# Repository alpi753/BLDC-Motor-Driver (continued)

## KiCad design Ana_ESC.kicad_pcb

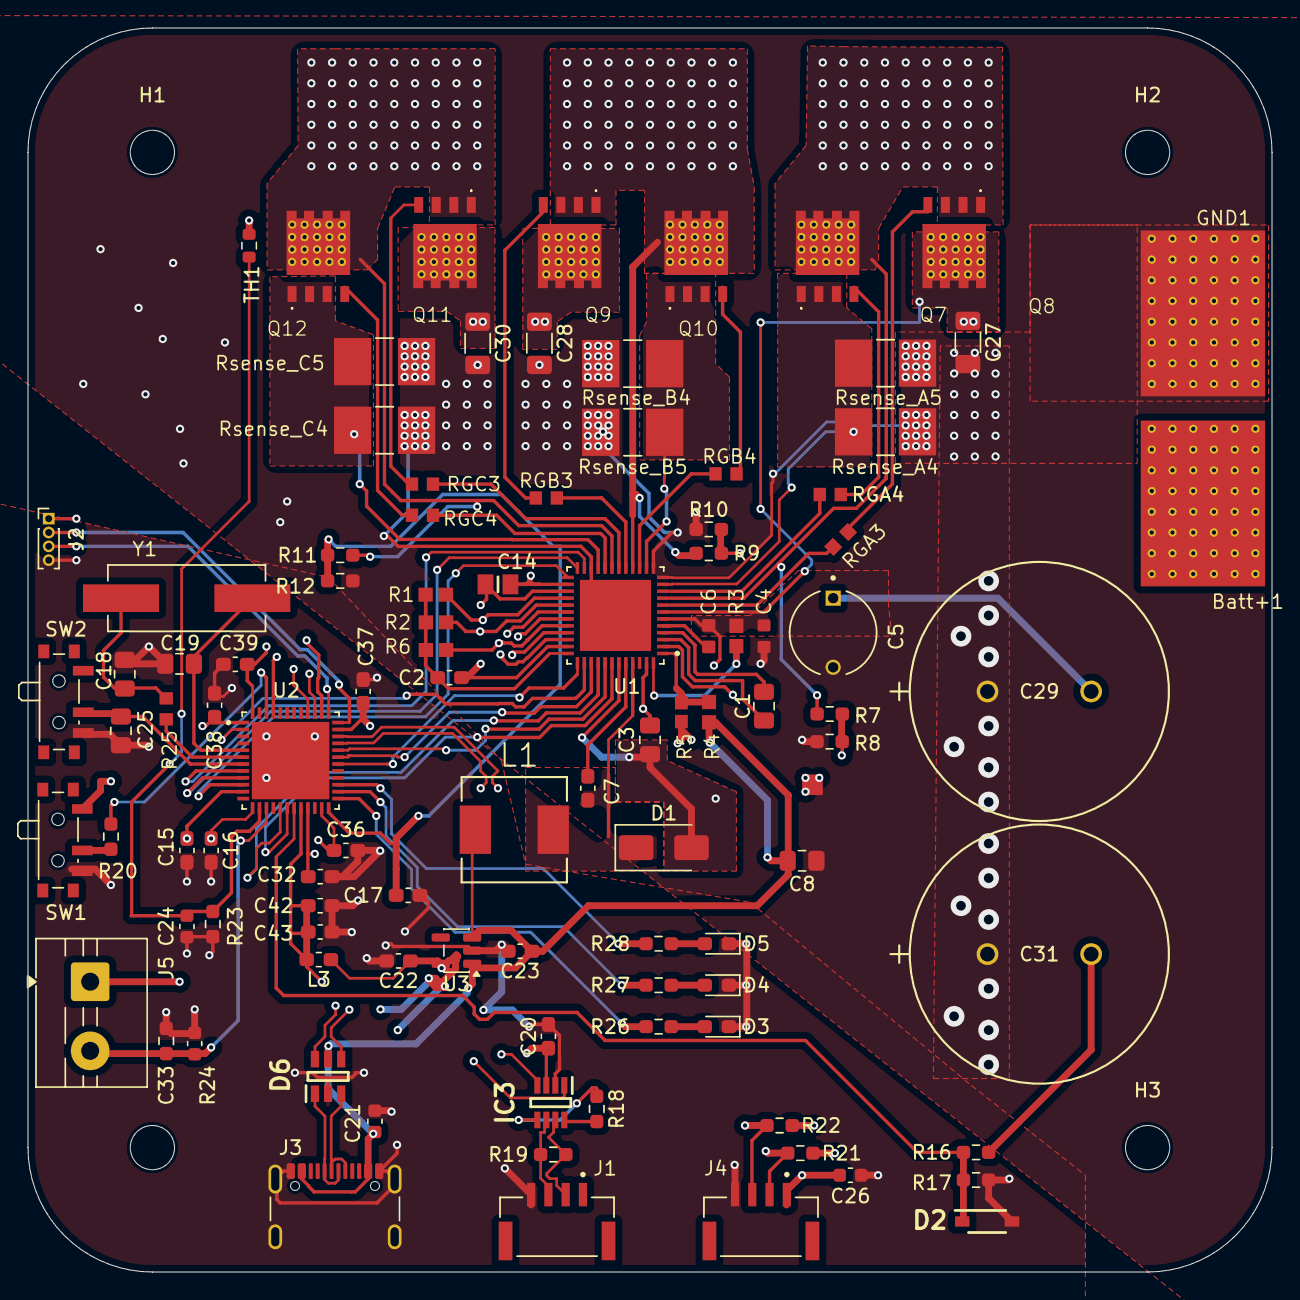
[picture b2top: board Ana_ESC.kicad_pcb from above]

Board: 4 copper layers, 90.0 x 90.0 mm, 105 parts (0 on the bottom side), 79 nets.

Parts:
Batt+1: power_pad_smd; Power_pad_smd
C1, C3: 47nF 100V; C_0805_2012Metric_Pad1.18x1.45mm_HandSolder
C2: 1uF 6.3V; C_0603_1608Metric_Pad1.08x0.95mm_HandSolder
C4: 0.1 uF 100V; CAPC1608X90N
C5: 22uF 100V; CAPPRD500W50D630H1120
C6: 1uF 16V; CAPC1608X90N
C7: 0.1uF 16V; C_0603_1608Metric_Pad1.08x0.95mm_HandSolder
C8: 22uF 16V; C_0805_2012Metric_Pad1.18x1.45mm_HandSolder
C14: 0.1uF 6.3V; CAPC2012X140N
C15, C16, C17, C43: 10nF; C_0603_1608Metric_Pad1.08x0.95mm_HandSolder
C18, C19: 33pF; C_0805_2012Metric_Pad1.18x1.45mm_HandSolder
C20, C37, C38, C39: 100nF; C_0603_1608Metric_Pad1.08x0.95mm_HandSolder
C21, C26: 1uF; C_0603_1608Metric
C22, C23: 1u; C_0603_1608Metric_Pad1.08x0.95mm_HandSolder
C24, C33: 2.2uF; C_0603_1608Metric
C25: 100nF; C_0805_2012Metric_Pad1.18x1.45mm_HandSolder
C27, C28, C30: 2.2uF; C_1206_3216Metric_Pad1.33x1.80mm_HandSolder
C29, C31: 680uF 80V; 80ZLJ680MGC18X25
C32: 100n; C_0603_1608Metric_Pad1.08x0.95mm_HandSolder
C36: 4u7; C_0603_1608Metric_Pad1.08x0.95mm_HandSolder
C42: 1uF; C_0603_1608Metric_Pad1.08x0.95mm_HandSolder
D1: 80V 1A; D_SMA
D2: D_Zener; SOD3716X135N
D3: LEDA; LED_0603_1608Metric_Pad1.05x0.95mm_HandSolder
D4: LEDB; LED_0603_1608Metric_Pad1.05x0.95mm_HandSolder
D5: LEDC; LED_0603_1608Metric_Pad1.05x0.95mm_HandSolder
D6: USBLC6-2SC6Y; SOT95P280X145-6N
GND1: power_pad_smd; Power_pad_smd
H1, H2, H3, H4: MountingHole; MountingHole_3.2mm_M3
IC3: TCAN330DCNT; SOT65P280X145-8N
J1, J4: BM04B-GHS-TBT_LF__SN__N_; JST_BM04B-GHS-TBT_LF__SN__N_
J2: Conn_01x04_Pin; PinHeader_1x04_P1.00mm_Vertical
J3: USB_C_Receptacle_USB2.0_16P; USB_C_Receptacle_GCT_USB4105-xx-A_16P_TopMnt_Horizontal
J5: Conn_01x02_Socket; TerminalBlock_MaiXu_MX126-5.0-02P_1x02_P5.00mm
L1: 22uH 1.6A; INDM7676X355N
L3: 100MHz / 1kR; L_0603_1608Metric_Pad1.05x0.95mm_HandSolder
NT2: NetTie_4; NetTie-4_SMD_Pad0.5mm
Q7, Q8, Q9, Q10, Q11, Q12: STL90N6F7; STL90N6F7_Thermal_Vias
R1, R2, R6: 10K; RESC1607X60N
R3: 100K; RESC1607X60N
R4: 5k6; RESC1607X60N
R5: 1k; RESC1508X50N
R7, R9, R11: 91k; R_0603_1608Metric_Pad0.98x0.95mm_HandSolder
R8, R10, R12: 4k7; R_0603_1608Metric_Pad0.98x0.95mm_HandSolder
R16: 3.3k; R_0603_1608Metric_Pad0.98x0.95mm_HandSolder
R17: 100k; R_0603_1608Metric_Pad0.98x0.95mm_HandSolder
R18, R20, R21, R22: 10k; R_0603_1608Metric_Pad0.98x0.95mm_HandSolder
R19: 120R; R_0603_1608Metric_Pad0.98x0.95mm_HandSolder
R23, R24: R_Small; R_0603_1608Metric_Pad0.98x0.95mm_HandSolder
R25: 0 ohm; RESC1508X55N
R26, R27, R28: 330R; R_0603_1608Metric_Pad0.98x0.95mm_HandSolder
RGA3, RGA4: 0ohm; RESC1508X55N
RGB3, RGB4: 0ohm; RESC1508X55N
RGC3, RGC4: 0ohm; RESC1508X55N
Rsense_A4, Rsense_A5: 2mohm; RESC6432X80N
Rsense_B4, Rsense_B5: 2mohm; RESC6432X80N
Rsense_C4, Rsense_C5: 2mohm; RESC6432X80N
SW1, SW2: SW_SPDT; SW_SPDT_PCM12
TH1: ERT-J1VG103FA; R_0603_1608Metric
U1: DRV8323RSRGZR; QFN50P700X700X100-49N
U2: STM32G431CBU6; QFN50P700X700X60-49N
U3: ME6211C33M5; SOT-23-5
Y1: ECS-80-20-5PX-TR; XTAL_ECS-80-20-5PX-TR

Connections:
+3.3V: C14.2, C20.1, C22.1, C26.1, C36.1, C37.1, C38.1, C39.1, IC3.3 (VCC), J2.1, J4.1, J5.1, L3.1, R21.1, R22.1, SW1.1 (A), TH1.1, U1.26 (VREF), U2.1 (VBAT), U2.23 (VDD), U2.35 (VDD), U2.48 (VDD), U3.5 (V_{OUT})
+3.3VA: C32.1, C42.1, C43.1, L3.2, U2.20 (VREF+), U2.21 (VDDA)
/Gate_Driver/AGND: C2.2, C14.1, NT2.4, R5.2, U1.27 (DGND), U1.35 (AGND)
/Gate_Driver/BGND: C3.1, D1.2 (A), NT2.2, U1.43 (BGND)
/Gate_Driver/DVDD: C2.1, R1.2, R2.2, R6.2, U1.36 (DVDD)
/Gate_Driver/FAULT: R1.1, U1.28 (FAULT_N)
/Gate_Driver/GHA: RGA3.1, U1.8 (GHA)
/Gate_Driver/GHB: RGB3.1, U1.17 (GHB)
/Gate_Driver/GHC: RGC3.1, U1.18 (GHC)
/Gate_Driver/GLA: RGA4.1, U1.10 (GLA)
/Gate_Driver/GLB: RGB4.1, U1.15 (GLB)
/Gate_Driver/GLC: RGC4.1, U1.20 (GLC)
/Gate_Driver/INHA: U1.37 (INHA), U2.30 (PA8)
/Gate_Driver/INHB: U1.39 (INHB), U2.31 (PA9)
/Gate_Driver/INHC: U1.41 (INHC), U2.32 (PA10)
/Gate_Driver/INLA: U1.38 (INLA), U2.2 (PC13)
/Gate_Driver/INLB: U1.40 (INLB), U2.17 (PB0)
/Gate_Driver/INLC: U1.42 (INLC), U2.18 (PB1)
/Gate_Driver/PGND: NT2.3, U1.2 (PGND)
/Gate_Driver/SCS: R6.1, U1.32 (SCS_N)
/Gate_Driver/SDO: R2.1, U1.29 (SDO)
/Gate_Driver/SENS1: C15.1, R7.2, R8.2, U2.11 (PA3)
/Gate_Driver/SENS2: C16.1, R9.2, R10.2, U2.13 (PA5)
/Gate_Driver/SENS3: C17.1, R11.2, R12.2, U2.24 (PB11)
/Gate_Driver/SHA: Q7.1 (S_1), Q7.2 (S_2), Q7.3 (S_3), Q8.5 (D_1), Q8.6 (D_2), Q8.7 (D_3), Q8.8 (D_4), Q8.9 (D_5), R7.1, U1.9 (SHA)
/Gate_Driver/SHB: Q9.1 (S_1), Q9.2 (S_2), Q9.3 (S_3), Q10.5 (D_1), Q10.6 (D_2), Q10.7 (D_3), Q10.8 (D_4), Q10.9 (D_5), R9.1, U1.16 (SHB)
/Gate_Driver/SHC: Q11.1 (S_1), Q11.2 (S_2), Q11.3 (S_3), Q12.5 (D_1), Q12.6 (D_2), Q12.7 (D_3), Q12.8 (D_4), Q12.9 (D_5), R11.1, U1.19 (SHC)
/Gate_Driver/SOA: U1.25 (SOA), U2.10 (PA2)
/Gate_Driver/SOB: U1.24 (SOB), U2.9 (PA1)
/Gate_Driver/SOC: U1.23 (SOC), U2.8 (PA0)
/Gate_Driver/SPB: Q10.1 (S_1), Q10.2 (S_2), Q10.3 (S_3), Rsense_B4.2, Rsense_B5.2, U1.14 (SPB)
/Gate_Driver/SPC: Q12.1 (S_1), Q12.2 (S_2), Q12.3 (S_3), Rsense_C4.2, Rsense_C5.2, U1.21 (SPC)
/MCU/BOOT0: R20.2, U2.46 (PB8-BOOT0)
/MCU/CAN+: IC3.7 (CANH), J1.2, R19.2
/MCU/CAN-: IC3.6 (CANL), J1.3, R19.1
/MCU/D+: D6.3 (I/O2_1), J3.A6 (D+), J3.B6 (D+)
/MCU/D-: D6.1 (I/O1_1), J3.A7 (D-), J3.B7 (D-)
/MCU/I2C1_SCL: J4.2, R21.2, U2.38 (PA15)
/MCU/I2C1_SDA: J4.3, R22.2, U2.45 (PB7)
/MCU/NTC_FET: C24.1, R23.1, TH1.2, U2.14 (PA6)
/MCU/NTC_MTR: C33.1, J5.2, R24.1, U2.15 (PA7)
/MCU/PD2: IC3.8 (S), R18.2
/MCU/RST: C25.1, SW2.2 (B), U2.7 (PG10-~RST)
/MCU/SWCLK: J2.3, U2.37 (PA14)
/MCU/SWDIO: J2.2, U2.36 (PA13)
/MCU/UART_N: IC3.4 (RXD), U2.39 (PC10)
/MCU/UART_P: IC3.1 (TXD), U2.40 (PC11)
/MCU/USB_DN: D6.6 (I/O1_2), U2.33 (PA11)
/MCU/USB_DP: D6.4 (I/O2_2), U2.34 (PA12)
/MCU/VBus: D2.1 (K), R16.2, R17.1, U2.19 (PB2)
/Mosfetv2/A+: Q8.1 (S_1), Q8.2 (S_2), Q8.3 (S_3), Rsense_A4.2, Rsense_A5.2, U1.11 (SPA)
GND: C15.2, C16.2, C17.2, C18.2, C19.2, C20.2, C21.2, C22.2, C23.2, C24.2, C25.2, C26.2, C32.2, C33.2, C36.2, C37.2, C38.2, C39.2, C42.2, C43.2, D2.2 (A), D3.1 (K), D4.1 (K), D5.1 (K), D6.2 (GND), IC3.2 (GND), J1.4, J2.4, J3.A1 (GND), J3.A12 (GND), J3.B1 (GND), J3.B12 (GND), J3.S1 (SHIELD), J4.4, R17.2, R23.2, R24.2, SW1.3 (C), SW2.3 (C), U2.49 (VSS), U3.2 (V_{SS})
MCU_PWR: C8.2, C21.1, C23.1, D6.5 (VBUS), J3.A4 (VBUS), J3.A9 (VBUS), J3.B4 (VBUS), J3.B9 (VBUS), L1.1, R4.2, U3.1 (V_{IN}), U3.3 (CE)
unnamed: C18.1, R25.1, Y1.1
unnamed: C7.1, D1.1 (K), L1.2, U1.45 (SW)
unnamed: D3.2 (A), R26.1
unnamed: D4.2 (A), R27.1
unnamed: D5.2 (A), R28.1
unnamed: IC3.5 (SHDN), R18.1
unnamed: Q7.4 (G), RGA3.2
unnamed: Q8.4 (G), RGA4.2
unnamed: Q9.4 (G), RGB3.2
unnamed: Q10.4 (G), RGB4.2
unnamed: Q11.4 (G), RGC3.2
unnamed: Q12.4 (G), RGC4.2
unnamed: R20.1, SW1.2 (B)
unnamed: C7.2, U1.44 (CB)
unnamed: C1.2, U1.4 (CPH)
unnamed: C1.1, U1.3 (CPL)
unnamed: R4.1, R5.1, U1.1 (FB)
unnamed: R3.2, U1.48 (SHDN_N)
unnamed: C6.1, U1.5 (VCP)
unnamed: R26.2, U2.25 (PB12)
unnamed: R27.2, U2.26 (PB13)
unnamed: R28.2, U2.27 (PB14)
unnamed: C19.1, U2.5 (PF0-OSC_IN), Y1.2
unnamed: R25.2, U2.6 (PF1-OSC_OUT)
PGND_DRV: C4.2, C5.N, C8.1, C27.2, C28.2, C29.1, C30.2, C31.1, GND1.1, NT2.1, R8.1, R10.1, R12.1, Rsense_A4.1, Rsense_A5.1, Rsense_B4.1, Rsense_B5.1, Rsense_C4.1, Rsense_C5.1, U1.12 (SNA), U1.13 (SNB), U1.22 (SNC), U1.49 (EP)
VM: Batt+1.1, C3.2, C4.1, C5.P, C6.2, C27.1, C28.1, C29.2, C30.1, C31.2, Q7.5 (D_1), Q7.6 (D_2), Q7.7 (D_3), Q7.8 (D_4), Q7.9 (D_5), Q9.5 (D_1), Q9.6 (D_2), Q9.7 (D_3), Q9.8 (D_4), Q9.9 (D_5), Q11.5 (D_1), Q11.6 (D_2), Q11.7 (D_3), Q11.8 (D_4), Q11.9 (D_5), R3.1, R16.1, U1.6 (VM), U1.7 (VDRAIN), U1.47 (VIN)

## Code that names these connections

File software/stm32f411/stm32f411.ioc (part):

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Mcu.Name=STM32F411C(C-E)Ux
Mcu.Package=UFQFPN48
Mcu.UserName=STM32F411CEUx
PA0-WKUP.GPIOParameters=GPIO_Label
PA0-WKUP.GPIO_Label=ADC_Ph0_Curr
PA0-WKUP.Signal=ADCx_IN0
PA1.GPIOParameters=GPIO_Label
PA1.GPIO_Label=ADC_Ph1_Curr
PA1.Signal=ADCx_IN1
PA10.GPIOParameters=GPIO_Label
PA10.GPIO_Label=INHC
PA10.Signal=S_TIM1_CH3
PA11.Mode=Device_Only
PA11.Signal=USB_OTG_FS_DM
PA12.Mode=Device_Only
PA12.Signal=USB_OTG_FS_DP
PA13.Mode=Serial_Wire
PA13.Signal=SYS_JTMS-SWDIO
PA14.Mode=Serial_Wire
PA14.Signal=SYS_JTCK-SWCLK
PA2.GPIOParameters=GPIO_Label
PA2.GPIO_Label=ADC_Ph2_Curr
PA2.Signal=ADCx_IN2
PA3.GPIOParameters=GPIO_Label
PA3.GPIO_Label=SENS1
PA3.Signal=GPIO_Input
PA4.Signal=GPIO_Input
PA5.GPIOParameters=GPIO_Label
PA5.GPIO_Label=V_Bus_Sense
PA5.Signal=ADCx_IN5
PA6.GPIOParameters=GPIO_Label
PA6.GPIO_Label=NTC_FET
PA6.Signal=ADCx_IN6
PA7.GPIOParameters=GPIO_Label
PA7.GPIO_Label=NTC_MTR
PA7.Signal=ADCx_IN7
PA8.GPIOParameters=GPIO_Label
PA8.GPIO_Label=INHA
PA8.Signal=S_TIM1_CH1
PA9.GPIOParameters=GPIO_Label
PA9.GPIO_Label=INHB
PA9.Signal=S_TIM1_CH2
PB0.GPIOParameters=GPIO_Label
PB0.GPIO_Label=INLB
PB0.Mode=PWM Generation2 CH2 CH2N
PB0.Signal=TIM1_CH2N
PB1.GPIOParameters=GPIO_Label
PB1.GPIO_Label=INLC
PB1.Mode=PWM Generation3 CH3 CH3N
PB1.Signal=TIM1_CH3N
PB13.GPIOParameters=GPIO_Label
PB13.GPIO_Label=PROT_D4
PB13.Signal=GPIO_Input
PB14.GPIOParameters=GPIO_Label
PB14.GPIO_Label=PROT_D5
PB14.Signal=GPIO_Input
PB2.GPIOParameters=GPIO_Speed,GPIO_Label
PB2.GPIO_Label=SPI1_CS
PB2.GPIO_Speed=GPIO_SPEED_FREQ_VERY_HIGH
PB2.Signal=GPIO_Output
PB3.Mode=Full_Duplex_Master
PB3.Signal=SPI1_SCK
PB4.Mode=Full_Duplex_Master
PB4.Signal=SPI1_MISO
PB5.Mode=Full_Duplex_Master
PB5.Signal=SPI1_MOSI
PB6.GPIOParameters=GPIO_Speed,GPIO_Label
PB6.GPIO_Label=SPI1_EN
PB6.GPIO_Speed=GPIO_SPEED_FREQ_VERY_HIGH
PB6.Signal=GPIO_Output
PB7.GPIOParameters=GPIO_Label
PB7.GPIO_Label=SPI1_FAULT
PB7.Signal=GPIO_Input
PC13-ANTI_TAMP.GPIOParameters=GPIO_Speed,GPIO_Label
PC13-ANTI_TAMP.GPIO_Label=INLA
PC13-ANTI_TAMP.GPIO_Speed=GPIO_SPEED_FREQ_HIGH
PC13-ANTI_TAMP.Signal=GPIO_Output
PH0\ -\ OSC_IN.Mode=HSE-External-Oscillator
PH0\ -\ OSC_IN.Signal=RCC_OSC_IN
PH1\ -\ OSC_OUT.Mode=HSE-External-Oscillator
PH1\ -\ OSC_OUT.Signal=RCC_OSC_OUT
RCC.HSE_VALUE=25000000
RCC.SYSCLKFreq_VALUE=72000000
RCC.SYSCLKSource=RCC_SYSCLKSOURCE_PLLCLK
board=custom

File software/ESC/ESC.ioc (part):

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Mcu.Name=STM32G431C(6-8-B)Ux
Mcu.Package=UFQFPN48
Mcu.UserName=STM32G431CBUx
PA0.GPIOParameters=GPIO_Label
PA0.GPIO_Label=Curr_Sense_A
PA0.Mode=IN1-Single-Ended
PA0.Signal=ADC1_IN1
PA1.GPIOParameters=GPIO_Label
PA1.GPIO_Label=Curr_Sense_B
PA1.Mode=IN2-Single-Ended
PA1.Signal=ADC1_IN2
PA10.GPIOParameters=GPIO_Label
PA10.GPIO_Label=INHC
PA10.Signal=S_TIM1_CH3
PA11.Mode=Device
PA11.Signal=USB_DM
PA12.Mode=Device
PA12.Signal=USB_DP
PA13.Mode=Serial_Wire
PA13.Signal=SYS_JTMS-SWDIO
PA14.Mode=Serial_Wire
PA14.Signal=SYS_JTCK-SWCLK
PA15.Mode=I2C
PA15.Signal=I2C1_SCL
PA2.GPIOParameters=GPIO_Label
PA2.GPIO_Label=Curr_Sense_C
PA2.Mode=IN3-Single-Ended
PA2.Signal=ADC1_IN3
PA6.GPIOParameters=GPIO_Label
PA6.GPIO_Label=NTC_Mosfet
PA6.Mode=IN3-Single-Ended
PA6.Signal=ADC2_IN3
PA7.GPIOParameters=GPIO_Label
PA7.GPIO_Label=NTC_Motor
PA7.Mode=IN4-Single-Ended
PA7.Signal=ADC2_IN4
PA8.GPIOParameters=GPIO_Label
PA8.GPIO_Label=INHA
PA8.Signal=S_TIM1_CH1
PA9.GPIOParameters=GPIO_Label
PA9.GPIO_Label=INHB
PA9.Signal=S_TIM1_CH2
PB0.GPIOParameters=GPIO_Label
PB0.GPIO_Label=INLB
PB0.Mode=PWM Generation2 CH2 CH2N
PB0.Signal=TIM1_CH2N
PB1.GPIOParameters=GPIO_Label
PB1.GPIO_Label=INLC
PB1.Mode=Output Compare3 CH3 CH3N
PB1.Signal=TIM1_CH3N
PB2.GPIOParameters=GPIO_Label
PB2.GPIO_Label=V_Bus_Sense
PB2.Mode=IN12-Single-Ended
PB2.Signal=ADC2_IN12
PB7.Mode=I2C
PB7.Signal=I2C1_SDA
PB8-BOOT0.Mode=FDCAN_Activate
PB8-BOOT0.Signal=FDCAN1_RX
PB9.Mode=FDCAN_Activate
PB9.Signal=FDCAN1_TX
PC10.Mode=Asynchronous
PC10.Signal=UART4_TX
PC11.Mode=Asynchronous
PC11.Signal=UART4_RX
PC13.GPIOParameters=GPIO_Label
PC13.GPIO_Label=INLA
PC13.Mode=PWM Generation1 CH1 CH1N
PC13.Signal=TIM1_CH1N
PC15-OSC32_OUT.Signal=GPXTI15
PF0-OSC_IN.Mode=HSE-External-Oscillator
PF0-OSC_IN.Signal=RCC_OSC_IN
PF1-OSC_OUT.Mode=HSE-External-Oscillator
PF1-OSC_OUT.Signal=RCC_OSC_OUT
RCC.HSE_VALUE=8000000
RCC.SYSCLKFreq_VALUE=168000000
RCC.SYSCLKSource=RCC_SYSCLKSOURCE_PLLCLK
board=custom

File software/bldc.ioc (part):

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Mcu.Name=STM32G431C(6-8-B)Ux
Mcu.Package=UFQFPN48
Mcu.UserName=STM32G431CBUx
PA0.GPIOParameters=GPIO_Label
PA0.GPIO_Label=CURR_A
PA0.Mode=IN1-Single-Ended
PA0.Signal=ADC1_IN1
PA1.GPIOParameters=GPIO_Label
PA1.GPIO_Label=CURR_B
PA1.Mode=IN2-Single-Ended
PA1.Signal=ADC1_IN2
PA11.Mode=Device
PA11.Signal=USB_DM
PA12.Mode=Device
PA12.Signal=USB_DP
PA13.Mode=Serial_Wire
PA13.Signal=SYS_JTMS-SWDIO
PA14.Mode=Serial_Wire
PA14.Signal=SYS_JTCK-SWCLK
PA2.GPIOParameters=GPIO_Label
PA2.GPIO_Label=CURR_C
PA2.Mode=IN3-Single-Ended
PA2.Signal=ADC1_IN3
PA3.GPIOParameters=GPIO_Label
PA3.GPIO_Label=VOLT_B
PA3.Mode=IN4-Single-Ended
PA3.Signal=ADC1_IN4
PA5.GPIOParameters=GPIO_Label
PA5.GPIO_Label=VOLT_A
PA5.Mode=IN13-Single-Ended
PA5.Signal=ADC2_IN13
PA6.GPIOParameters=GPIO_Label
PA6.GPIO_Label=NTC_FET
PA6.Mode=IN3-Single-Ended
PA6.Signal=ADC2_IN3
PB10.GPIOParameters=PinState,GPIO_Label
PB10.GPIO_Label=SPI1_NSCS
PB10.PinState=GPIO_PIN_SET
PB10.Signal=GPIO_Output
PB11.GPIOParameters=GPIO_Label
PB11.GPIO_Label=VOLT_C
PB11.Mode=IN14-Single-Ended
PB11.Signal=ADC2_IN14
PB12.GPIOParameters=GPIO_Label
PB12.GPIO_Label=LEDC
PB12.Signal=GPIO_Output
PB13.GPIOParameters=GPIO_Label
PB13.GPIO_Label=LEDB
PB13.Signal=GPIO_Output
PB14.GPIOParameters=GPIO_Label
PB14.GPIO_Label=LEDA
PB14.Signal=GPIO_Output
PB15.GPIOParameters=GPIO_Label
PB15.GPIO_Label=SPI1_ENABLE
PB15.Signal=GPIO_Output
PB2.GPIOParameters=GPIO_Label
PB2.GPIO_Label=VBUS
PB2.Mode=IN12-Single-Ended
PB2.Signal=ADC2_IN12
PB3.Mode=Full_Duplex_Master
PB3.Signal=SPI1_SCK
PB4.Mode=Full_Duplex_Master
PB4.Signal=SPI1_MISO
PB5.Mode=Full_Duplex_Master
PB5.Signal=SPI1_MOSI
PF0-OSC_IN.Mode=HSE-External-Oscillator
PF0-OSC_IN.Signal=RCC_OSC_IN
PF1-OSC_OUT.Mode=HSE-External-Oscillator
PF1-OSC_OUT.Signal=RCC_OSC_OUT
RCC.HSE_VALUE=8000000
RCC.SYSCLKFreq_VALUE=16000000
board=custom

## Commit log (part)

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2026-02-20 Added existing files
    We need to think about:
    Sensorless FOC driving technique sensing method for knowing the position of rotor, and so we can activate related phases.
2026-03-10 lib file added -step file, symbol file and footprints-
2026-03-10 Notlar
2026-03-10 Update notes on motor driver circuit and Mosfet analysis
    Added general notes about the motor driver circuit and updated the analysis of the Mosfet driver IC's current limit.
2026-03-10 mosfet v2
2026-03-10 reference files added
2026-03-10 just a note added to notlar
2026-03-12 Component List added from Digikey
2026-03-12 MCU schematics update
2026-03-12 whakkjls
2026-03-12 cube ide file added for stm32g431
2026-03-12 some pins changes"
2026-03-21 nothing
2026-03-21 Revert "nothing"
    This reverts commit c8bc8ca9c45f61fe26da700702173eff74c7b1f5.
2026-03-21 current sense -> bemf switch
2026-03-21 added ntc sensor
2026-03-21 t git ignore
2026-03-21 vbus / current sense pins on MCU
2026-03-21 leds
2026-03-21 RST pin
2026-03-22 thermal calculations done and Shunt Resistors changed. Not 3, just 2 resistors can dissipate the power.
2026-03-24 Footprints prepared, first pcb project created.
2026-03-30 component list updated, all footprints updated and now they are compatible to produce with hand (no 0402 size)
2026-03-31 some tags chaneged, pcb thinked about pcb component placement, aluminum mosfet carrier pcb and paralelling mosfets
2026-04-10 starting with pcb (kicad_pcb (version 20241229) (generator "pcbnew") (generator_version "9.0") (layers (0 "F.Cu" signal) (2 "B.Cu" signal) (9 "F.Adhes" user "F.Adhesive") (11 "B.Adhes" user "B.Adhesi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
2026-04-10 d;akljadsl;kdsj
2026-04-10 started to pcb design, mosfets,shunts drv8323 placement.
2026-04-13 new pcb
2026-04-13 pcb - mcu part +
2026-04-15 all nıght 4/12
2026-04-22 Some pcb design and schematics editings about PGND_DRV
2026-04-22 all routed pcb
2026-04-25 fixing design errors
2026-05-11 New one_GND_Layer pcb desgin has finished yet. DRC Rule checks needs to be controlling and correcting still.
2026-05-11 some drc rule checks and correcting
2026-05-12 minor rule checking warning
2026-05-12 3d objects and pdf
2026-05-14 BOM list prepared for ekom and direnc.net
2026-05-14 for LCSC components the layout/footprints changed. Previous commit for ekom/direncnet components.
2026-06-17 arranged into hardware and software
2026-06-17 arranging git modules
2026-06-17 added cbor encoding
2026-06-17 removing builds
2026-06-17 universal BSP
2026-06-18 VSCode terminala seems to fuck up submodules
2026-06-18 git modules again! root cause- vscode
2026-06-18 proper random data for stm32f411
2026-06-18 python script to monitor prints
2026-06-18 commutaition implementation perhaps not working
2026-06-18 flsakj
2026-06-19 ADC DMA on stm32f411
2026-06-19 V bus sensing, power usage and
2026-06-19 readme and agenets updated
2026-06-19 FOC implementated
2026-06-19 dynamic loop speed for reading and transmittting, device id added to telem data
2026-06-19 consolidated headers into one
2026-06-19 console changes beed update
2026-06-19 Fixing "G431 uses polled ADC in the FOC loop — same path as telemetry snapshot."
2026-06-19 OC4Ref ADC1 PWM tripger to prevent interruption from codegen
2026-06-19 settings update
2026-06-19 drv8323 works in 8 bit
2026-06-19 fixing some startups strategyies
2026-06-19 console update, resolved some startup update settings
2026-06-19 moved files around
2026-06-19 increased heap sie and commThread stack size
2026-06-30 final project board layout is in this commit
